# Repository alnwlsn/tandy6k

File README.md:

***I am now putting my trs-80 stuff in [a new repo: trashcan80](https://github.com/alnwlsn/trashcan80)***

# tandy6k
stuff for my tandy 6000 computer project (and might be applicible to the TRS-80 Model II, TRS-80 Model 12, TRS-80 Model 16 or TRS-80 Model 16B)

- Keyboard circuitry explained: https://www.youtube.com/watch?v=PWalT-7FzVU

## 8inch-adapter-pcb
Single sided, CNC cut PCB for converting the 50 pin 8" floppy disk cable to the more common 34 pin cable. Based on this https://github.com/pski/fd50to34 and made so I could quickly cut one out and start using it. Intended for a Gotek floppy disk emulator with https://github.com/keirf/flashfloppy

It might only work with a Gotek. On that, you can assign pin 34 to Drive Ready, and pin 2 to Disk Changed. On a real 5" or 3.5" drive, pin 34 is usually Disk Changed (but you can sometimes jumper it to drive ready instead), and pin 2 is used to select the density or disk RPM. 

**Update** - After nearly a week of confusing symptoms, I discovered that in some cases, the 6000 really does care if the disk drive reports 1 or 2 sided media. The Xenix install floppies come on both types, and the install will fail if the wrong type is used (you will get HRDIOE). I isolated pin 10 on the 50 pin side - this should be connected to a switch or jumper to GND; if you want to report 2 sided media, close the switch. Otherwise, leave it open.

## ps2-keyboard
Converts a ps2 keyboard to one that works with a TRS-80 8-inch system. Made because I was getting impatient waiting to fix the broken keyboard I have. Runs on an Arduino pro micro, but similar things should work. Similar to this converter https://www.smbaker.com/tandy-1000-upgrades-ps2-tandy-keyboard-adapter but for the Tandy 6000 instead of the Tandy 1000, and made more lazily by using the Arduino framework. Uses this PS2 arduino library https://github.com/techpaul/PS2KeyAdvanced

Change the mapping how you wish; I have not checked it against the real tandy 6000 keyboard, but it seems to mostly work well anyways. 

# Misc Notes
* installing 2nd bank of DRAM for 128K on z80 board (or how I learned to read the instructions)
  * Be sure to remove C81-C83, if not already removed. These are used as power bypass caps for 16K rams, but for 64K rams, an address signal is on those pins instead. If the caps are present, they stretch the signal out too much and it doesn't work, which is why they must be cut out. See model 12/16 technical bullitin #18.

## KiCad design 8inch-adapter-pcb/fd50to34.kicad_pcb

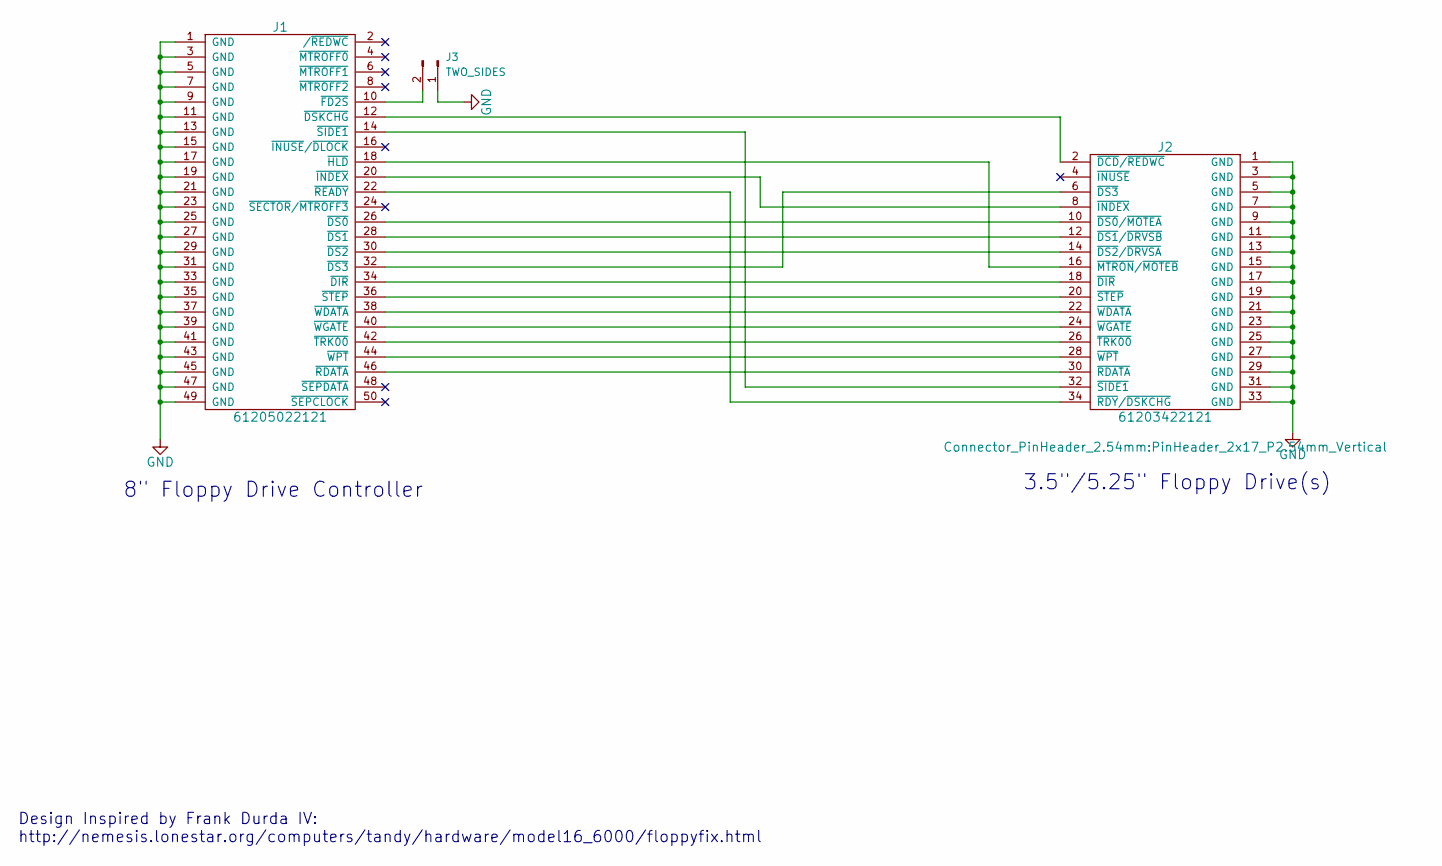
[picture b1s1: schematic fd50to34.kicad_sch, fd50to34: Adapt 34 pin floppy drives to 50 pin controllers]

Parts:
J1: 61205022121; PinHeader_2x25_P2.54mm_Vertical; PartNum 61205022121
J2: 61203422121; PinHeader_2x17_P2.54mm_Vertical; PartNum 61203422121
J3: TWO_SIDES; PinHeader_1x02_P2.54mm_Vertical

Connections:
GND: J1.1 (GND), J1.3 (GND), J1.5 (GND), J1.7 (GND), J1.9 (GND), J1.11 (GND), J1.13 (GND), J1.15 (GND), J1.17 (GND), J1.19 (GND), J1.21 (GND), J1.23 (GND), J1.25 (GND), J1.27 (GND), J1.29 (GND), J1.31 (GND), J1.33 (GND), J1.35 (GND), J1.37 (GND), J1.39 (GND), J1.41 (GND), J1.43 (GND), J1.45 (GND), J1.47 (GND), J1.49 (GND), J2.1 (GND), J2.3 (GND), J2.5 (GND), J2.7 (GND), J2.9 (GND), J2.11 (GND), J2.13 (GND), J2.15 (GND), J2.17 (GND), J2.19 (GND), J2.21 (GND), J2.23 (GND), J2.25 (GND), J2.27 (GND), J2.29 (GND), J2.31 (GND), J2.33 (GND), J3.1
unnamed: J1.34 (~DIR), J2.18 (~DIR)
unnamed: J1.26 (~DS0), J2.10 (~DS0/~MOTEA)
unnamed: J1.28 (~DS1), J2.12 (~DS1/~DRVSB)
unnamed: J1.30 (~DS2), J2.14 (~DS2/~DRVSA)
unnamed: J1.32 (~DS3), J2.6 (~DS3)
unnamed: J1.12 (~DSKCHG), J2.2 (~DCD/~REDWC)
unnamed: J1.10 (~FD2S), J3.2
unnamed: J1.18 (~HLD), J2.16 (~MTRON/~MOTEB)
unnamed: J1.20 (~INDEX), J2.8 (~INDEX)
unnamed: J1.46 (~RDATA), J2.30 (~RDATA)
unnamed: J1.22 (~READY), J2.34 (~RDY/~DSKCHG)
unnamed: J1.14 (~SIDE1), J2.32 (~SIDE1)
unnamed: J1.36 (~STEP), J2.20 (~STEP)
unnamed: J1.42 (~TRK00), J2.26 (~TRK00)
unnamed: J1.38 (~WDATA), J2.22 (~WDATA)
unnamed: J1.40 (~WGATE), J2.24 (~WGATE)
unnamed: J1.44 (~WPT), J2.28 (~WPT)

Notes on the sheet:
3.5"/5.25" Floppy Drive(s)
Design Inspired by Frank Durda IV: http://nemesis.lonestar.org/computers/tandy/hardware/model16_6000/floppyfix.html
8" Floppy Drive Controller

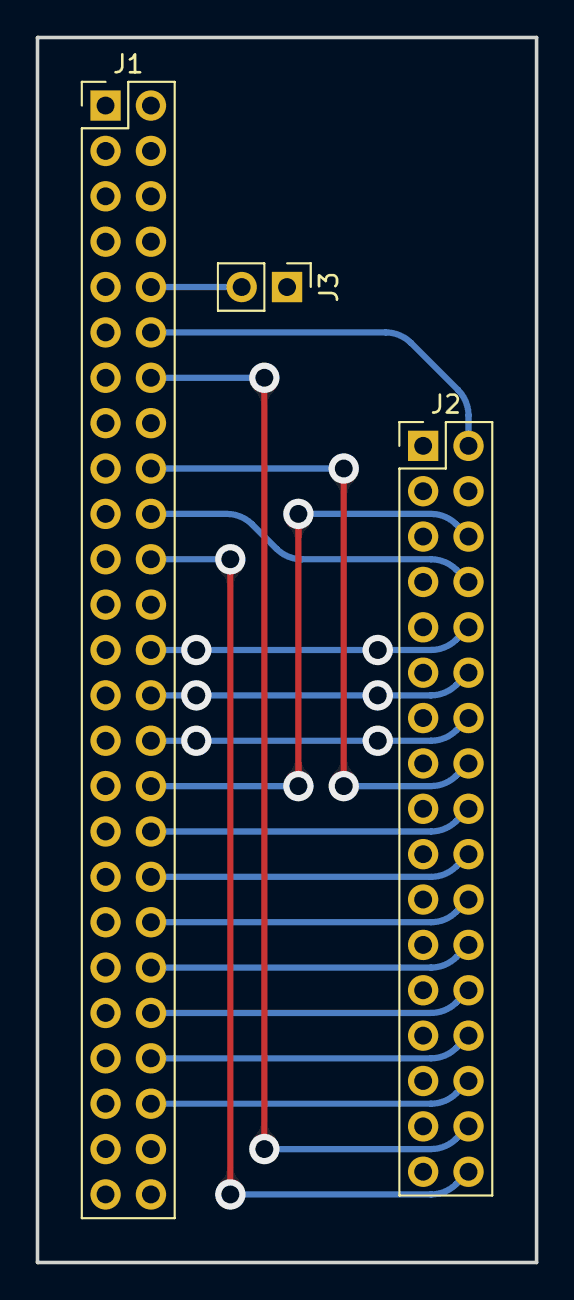
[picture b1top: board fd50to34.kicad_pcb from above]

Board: 2 copper layers, 27.9 x 68.6 mm, 3 parts (0 on the bottom side), 18 nets.

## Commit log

2023-09-10 added ps2 keyboard stuff
2023-09-10 added floppy pcb stuff
2023-09-16 rev2 pcb
2023-09-17 2 sided fix
2024-01-17 moving this repo
